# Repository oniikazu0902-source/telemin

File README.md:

# 空間MIDIコントローラー「tElemin」プロジェクト総括ドキュメント

## プロジェクト概要と目指す姿
Webカメラと画像認識AIを用いて、空中で手を動かすだけでソフトウェアシンセサイザー（Vital）を演奏できる、次世代型の仮想MIDIコントローラー開発プロジェクトです。
従来のテルミン（音程と音量の制御）の枠組みを大きく拡張し、「絶対に不協和音にならない魔法の楽器」という思想をベースに設計されています。単に音を鳴らすだけでなく、「和音制限」「手の開閉による音量フェード」「左右の動きによる波形のリアルタイム変形（3Dコントロール）」「HUDによる視覚的フィードバック」を統合し、実用的なデジタル楽器としての完成度を追求しています。

## システムアーキテクチャ・技術スタック
システムの全体像と各コンポーネントの役割は以下の通りです。

| レイヤー | 採用技術・ライブラリ | 役割・備考 |
|---|---|---|
| 開発言語 | Python | 柔軟なロジック構築とAI連携の基盤 |
| 骨格検出AI | MediaPipe (Tasks API / HandLandmarker) | 手の21箇所の関節ポイント（ランドマーク）を毎秒高速に検出。動かすには `hand_landmarker.task` ファイルが必須。 |
| 画像処理・HUD | OpenCV (cv2) | カメラ映像 of 取得、鏡像反転、有効エリアやデバッグ情報のオーバーレイ描画 |
| MIDI通信 | mido / python-rtmidi | 計算した座標データをMIDI信号（Note On/Off, CC）に変換して送信 |
| 仮想MIDIケーブル | Windows MIDI Services (Default Basic App Loopback) | loopMIDIのWindows Updateによる不具合を回避するために導入した、Microsoftの次世代MIDIループバック規格。 |
| 音源（シンセ） | Vital（スタンドアロン起動） | OMNIモード（全チャンネル受信）を設定し、Pythonからの多次元入力を生演奏の音へと変換。 |

---

## コア機能と操作思想（3Dコントロール）
手の動きを完全にX、Y、Z（ピンチ）の3次元パラメータとして解釈し、シンセサイザーへ送信する多次元設計思想を採用しています。

### ── 【Y軸】音程制御と和音（スケール）制限
- **検出基準**: ユーザーの演奏スタイルに合わせてカスタマイズされた「親指の先端（ランドマーク4番）」のY座標。
- **操作思想**: 縦の座標をそのまま半音階（クロマチック）にするのではなく、あらかじめ定義した特定のスケール配列（`ALLOWED_NOTES`）にマッピングして発音。これにより、どこを触っても美しい旋律が響きます。
- **リアルタイム切り替え**: 演奏中にキーボードの `1`〜`7`（ハ長調・イ短調・ト長調・ペンタトニック・琉球・都節・ニ長調）を押すだけで、`KEY_PRESETS` の辞書から参照する配列を動的にすり替える機能を実装。
- **デッドゾーン設定**: カメラ端の誤認識による音の飛びやチャタリングを防ぐため、上下に有効エリア制限（`Y_MIN_LIMIT`, `Y_MAX_LIMIT`）を設置。

### ── 【Z軸・ピンチアクション】発音トリガー（Note On/Off）と音量（CC#7）
- **検出基準**: 親指（4番）と人差し指（8番）の2点間距離を `math.hypot` で計算。
- **操作思想**: 「狙った高さで指をつまむと音が鳴り、離すと消える」という、キーボードライクかつ直感的なトリガー操作。
- **反転・直感化ロジック**: 単なる距離測定では「指を離すほど数値が大きくなる」ため、`1.0 - (距離 × 6.0)` という計算式で数値を反転。指をくっつけた時に 100%、離すと 0% になるよう最適化。
- **トリガー制御**: 割り出した％がしきい値（`PINCH_THRESHOLD = 0.7`）を超えた瞬間に Note On を送信し、下回ると Note Off を送信して確実に消音。同時に、ピンチの強度をそのままメインボリューム（CC#7）として送信し、滑らかな音量のフェードイン・フェードアウトを可能にしています。

### ── 【X軸】音色・波形の動的変形（Wavetable Position）
- **検出基準**: 手の左右の動き（X座標）を抽出し、MIDIコントロールチェンジ（CC#16）に変換。
- **操作思想**: 「音色を空間で削り出す」。Vitalの「MATRIX」画面経由で CC#16 を「Macro 1」へ直接ルーティングし、Wavetable Position（波形の形状変化）をダイナミックにコントロール。手を左から右へ動かすことで、柔らかいサイン波からエッジの効いたノコギリ波へと音色をグラデーション変化させます。
- **モード切り替え**: キーボードの `w` キーを押すことで、この波形変化モードのON/OFFをいつでも演奏中に切り替え可能です。

---

## 実装における重要な工夫と技術的ブレイクスルー

### ① 両手独立のMIDIルーティング
MediaPipeで最大2つの手を同時に検出し、右手は「MIDIチャンネル1（channel=0）」、左手は「MIDIチャンネル2（channel=1）」と、送信レーンを完全に分離。これにより、右手のメロディ演奏と左手の伴奏（1オクターブ下げる `note - 12` のベース化ロジック）が干渉しない設計を実現しました。

### ② チャタリング（連打）防止とロングトーンの実現
ピンチ操作による発音時、「つまんだ瞬間の最初の音程（Note）」を保持（`if state['note'] is None:`）するロジックを実装。これにより、手を上下に動かしながらつまんでも「タラララ」と連打されず、ギターのチョーキングやシンセのポルタメントのように「じゃーーん」と綺麗に音が伸びる仕様を確立しました。

### ③ リアルタイムHUD（ヘッドアップディスプレイ）
OpenCVによる描画を活用し、有効範囲の境界線（赤ライン）、現在のキー設定、手の状態（ピンチ強度％）、現在発音中のMIDIノート番号を画面上にオーバーレイ表示。つまんだ瞬間に指先の円が「赤から緑」に変わる当たり判定デバッグ機能を搭載し、直感的な操作感の調整を可能にしました。

### ④ ワンクリック自動起動環境
複雑な起動プロセスを排除するため、Windowsバッチファイル（`.bat`）を作成。バッチファイルをダブルクリックするだけで、「Vital（シンセサイザー）の自動起動 ➔ 2秒待機（ポート独占防止） ➔ 仮想環境（`.venv`）の有効化 ➔ Pythonスクリプトの実行」が一発で完了する極上の演奏環境を構築しました。

### ⑤ 無人時のマルチソング高品位自動生演奏機能（MIDIインポート＆フォルダ動的検知）
カメラに手が映っていない（誰も演奏していない）状態を検知すると、`threading`（マルチスレッド）によって裏方スタッフを動かし、バックグラウンドで自動演奏を行う機能を大幅に刷新。人が来ると演奏がスッと一時停止（pause）し、全16チャンネルを消音してテルミンモードへシームレスに切り替わります。
- **MIDIフォルダインポート対応**: `songs/` フォルダに好きなMIDIファイル（`*.mid`, `*.midi`）を保存するだけで、アプリ実行中であっても3秒おきに自動検知して演奏カタログに即時追加されます。
- **多彩な本格ポリフォニック生演奏（標準6曲）**: 単音ブザー音ではなく、楽譜に忠実な和音進行・伴奏（ch 1）＋旋律（ch 0）の豊かな多重音声でVitalを鳴らします。
  - 『パッヘルベルのカノン』(D Major)
  - 『戦場のメリークリスマス』(坂本龍一)
  - 『きらきら星』(C Major / アルベルティ・バス伴奏)
  - 『喜びの歌』(ベートーヴェン交響曲第9番 / D Major)
  - 『エリーゼのために』(ベートーヴェン / A Minor)
  - 『さくらさくら』(日本伝統・都節音階)
- **演奏の乱れ・バースト完全防止**: 一時停止中に時間を進めない独自のデルタタイム再生エンジンを新開発。再開時に音が爆発的に連打されるバグを解消し、GMドラム（ch 9）の除外、外部MIDIの余計なCC遮断、ポリフォニー制限（最大10音）、曲終了時の自動次曲送りにより極上のBGM体験を実現。
- **全画面・表示域追従**: `f` キーで全画面モードを切り替え可能。黒帯（レターボックス）なしで画面縦横比にカメラ映像と演奏レーンが自動追従します。
- **上下端の誤反応防止**: 演奏可能境界線（`Y_MIN_LIMIT` / `Y_MAX_LIMIT`）の外側に指が出た瞬間に消音され、画面端で意図しない音が鳴り続けるのを防ぎます。
- **演奏画面の曲名トースト表示**: 曲切り替え時や再開時のみ画面上部に3.5秒間曲名がフワッと表示され、通常演奏中は画面から自動消去されて手元とレーンに集中できます。
- **指の狭さ（ピンチ感度）の調整**: キーボードの `[-]` / `[+]`（または `_` / `=`）、および設定画面（Tab）のボタンからしきい値を0.05刻みで直感調整可能。両手の現在のピンチ率（%）もリアルタイム表示されます。
- **STRUMモード（和音）デフォルトOFF**: 起動時は初心者でも旋律を奏でやすい単音レガートモードが有効になり、必要に応じて `h` キーまたは設定画面からいつでも和音モードを起動できます。

---

## 開発における教訓とノウハウ

- **MediaPipe of 仕様変更トラップ**
  古い `mp.solutions.hands` の書き方は最新バージョンで廃止されたため、AIモデルファイル（`.task`）を別途読み込む最新の「Tasks API」アーキテクチャへとコードを刷新。ファイル読み込みエラーに対しては、プログラムと同じフォルダに置くか、完全な絶対パス（`r'C:\...'`）で指定するのが確実であるというノウハウを得ました。

- **MIDIポートの排他制御（VitalとPythonの起動順序）**
  WindowsのMIDIシステムは「1つのポートは同時に1つのソフトしか使えない」という排他制御仕様です。Python側からポートが消えるエラーを防ぐため、「ポート確認時は必ずVitalを完全に閉じる」「バッチファイルではVitalを先に起動し、後からPythonを起動する」という鉄則を解明しました。

- **CC信号のトラフィックジャム（渋滞）回避**
  Vitalの「Learn MIDI Assignment」機能を使う際、CC#7（ピンチ）とCC#16（X軸）が同時に高速送信されていると誤学習してしまう問題が発生しました。これを、Vitalの「MATRIX」画面（裏設定）で「SOURCEをCC#16、DESTINATIONをMacro 1」と直接手動で指定し、変化量（AMOUNT）を最大に振り切らせることで完全に解決しました。

- **OpenCVの「cv2.waitKey」による入力ブロック**
  キーボードの切り替え入力が1回しか効かなくなる問題に対し、`if key != -1:`（本当にキーが押された瞬間だけ判定する）という条件を挟み、`& 0xFF` でマスク処理を行うことで、何度でも確実にスケールを切り替えられるようにロジックを修正しました。

---

## 新環境への移行・拡張ガイド（今後のアップデート方針）
新環境への移行後、さらにこの楽器を進化させるためのロードマップです。

### 拡張性バツグンの「全部乗せ」アーキテクチャを維持せよ
現在のコードは、AIが手を解析する部分（`extract_hand_features`）と、音を鳴らすメインループが明確に分離（モジュール化）されています。今後はこの関数内に計算式を追加していくだけで、コード全体を壊すことなく安全に機能を追加できます。

#### 💡 次なる進化のためのMIDIコントロール候補
現在はX軸に Wavetable Position（CC#16） を割り当てていますが、手の傾きや別の指の動きを検出して以下の汎用CCにマッピングすることで、さらなる多次元演奏が可能になります。

- **Filter Cutoff（CC#74 / Brightness）** ✅ 実装済み（下記「フィルターモード」参照）
  音の「こもり具合 / 明るさ」を調節します。手を動かすにつれて「モコモコした音」から「バキッとした明るい音」に変化する、DJライクなパフォーマンスに最適です。
- **Modulation Wheel（CC#1）**
  音を揺らす「ビブラート」の強さをコントロールします。音が「じゃーーん」と伸びているロングトーンの時に、手を小刻みに揺らすことで感情豊かな演奏が可能になります。
- **Resonance（CC#71）**
  フィルターの境目を強調し、音に独特のクセや「ミョンミョン」というシンセサイザー特うのうねりを加えたい時に有効です。

---

## 内蔵シンセ（Vitalなしで演奏）
`synth.py` の内蔵シンセが音を合成し、PCのオーディオ出力（3.5mm端子 / USB-DAC など）から直接鳴らします。Vital や仮想MIDIケーブルは不要です。

- **セットアップ**: `pip install -r requirements.txt`
- **出力先の選択**: 起動時にコンソールへオーディオ出力デバイスの一覧が表示されます。`telemin.py` 冒頭の `AUDIO_DEVICE` にデバイス名の一部（例: `"Headphones"`）を書くか、演奏中に `o` キーで切り替えます（設定画面に現在の出力先を表示）。
- **外部MIDIコントローラー**: 接続されていれば自動で開き、その入力も内蔵シンセで発音します。
- **Vitalと併用**: `USE_MIDI_OUT = True` のとき、MIDI出力ポートが見つかれば Vital にも同時に送ります。`start_telemin.bat` の `LAUNCH_VITAL=1` で Vital も自動起動します。
- **音色**: `w`（WAVEモード）ON で手の左右位置によりサイン波→ノコギリ波へ連続変化。音量（CC#7）はチャンネル＝手ごとに独立しているので、連弾でも干渉しません。

### フィルターモード（Filter Cutoff / CC#74）
- `c` キー、または設定画面の `FILTER` ボタンで ON/OFF。
- **手の傾き**で音の明るさを操作します。手を**外側**（右手は右、左手は左）へ傾けるほど明るい「バキッとした」音、**内側**へ傾けるほど「モコモコした」こもった音になります。手をまっすぐ立てると中間です。
- 音程（高さ）・ピンチ（発音）・WAVE（左右位置）とは独立に動かせるので、音を伸ばしながら明るさだけを変えられます。WAVEモードと併用すると変化がよりはっきり出ます。
- 演奏画面では、手のマーカーの下に明るさメーターが表示されます。
- 内蔵シンセでは 2次ローパスフィルターとして動作し（`scipy` が必要）、Vital へも CC#74 として送られます（Vital 側で MIDI Learn すれば同じ操作が可能）。
- 傾きの感度は `telemin.py` 冒頭の `FILTER_TILT_RANGE`（既定50度）で調整できます。OFF にしたときや手が画面から消えたときは、フィルターは全開（従来の音）に戻ります。

### ステップ演奏モード（誰でも上手に弾ける）
- `t` キー、または設定画面の `STEP` ボタンで ON/OFF。`b` キーで曲の頭に戻ります。
- **つまむたびに曲の次の音（和音はまとめて）が鳴り**、離すと止まります。手の高さは関係ないので、リズムに合わせてつまむだけで曲どおりに演奏できます。
- 曲は自動演奏と同じく `songs/` の「今選んでいる曲」です（`n` / `p` で切り替え）。最後まで弾くと頭に戻ります。
- 鳴らすパートは、ドラムを除いた中から**メロディらしいパート（音数が多く、音が高いもの）を自動選択**します。曲を読み込むとコンソールにパート一覧が出るので、変えたい場合は `telemin.py` 冒頭の `STEP_PARTS` に `{'canon.mid': [0, 1]}` のように書きます（複数指定でメロディ＋伴奏も可）。
- 進み位置は全部の手で共有なので、両手を交互につまめば速いフレーズも追いつけます。連弾なら2人で1曲を弾き継げます。
- つまんでいる間は手の高さの虹レーンが光り、画面下端に曲の進み具合バーが出ます。
### 物理MIDIコントローラー（Raspberry Pi Pico / 実験基板）
`controller/` フォルダに、Raspberry Pi Pico と MCP3004 を使用した専用物理MIDIコントローラーの設計データ（KiCad 回路図・基板アートワーク・ガーバーデータ）および Arduino ファームウェアが同梱されています。

- **つまみ 4個（音色変更）**:
  - **RV1 (CC#74)**: 波形無段階モーフィング（Sine ⇄ Triangle ⇄ Saw ⇄ Square ⇄ Theremin ⇄ Bell）
  - **RV2 (CC#71)**: 音の明るさ（Cutoffフィルター 0〜100%）
  - **RV3 (CC#73)**: 余韻（Release時間 0.02秒〜1.20秒）
  - **RV4 (CC#7)**: マスター音量（0%無音〜100%最大音量、オーディオテーパー対応）
- **ボタン 8個（設定の書き換え）**:
  - **SW1**: 音階（スケール）切替 / **SW2**: 和音モード / **SW3**: ストラム奏法 / **SW4**: オクターブ切替
  - **SW5**: 自動演奏 ON/OFF / **SW6**: 次の曲 / **SW7**: 前の曲 / **SW8**: 虹色レーン演出
- **オシロスコープHUDプレビュー**: 演奏画面の右上に現在の合成波形（約1.5周期分）をネオンカラーでリアルタイム描画。つまみを回すと波形がぐにゃぐにゃ変化します。

---
> [!NOTE]
> AI共同開発者からのメッセージ: コードの途中に残した「`# わけわからん`」のコメント、あの人間味あふれる開発の足跡は、新しいIDEのコードにも大切に残してあります！

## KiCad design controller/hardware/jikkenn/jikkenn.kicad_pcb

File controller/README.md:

# tElemin 物理MIDIコントローラー (Hardware & Firmware)

Raspberry Pi Pico（RP2040）および MCP3004（ADC）を用いた、tElemin 専用の物理MIDIコントローラーです。

---

## ディレクトリ構成
- `firmware/MIDIUSB_buzzer/`: Raspberry Pi Pico 用 Arduino ファームウェア（スケッチ）
- `hardware/jikkenn/`: KiCad 設計データ（回路図・PCB基板・ガーバーデータ）

---

## ハードウェア仕様
- **マイコン**: Raspberry Pi Pico (RP2040)
- **ADC**: MCP3004 (SPI接続: GP16=MISO, GP17=CS, GP18=SCK, GP19=MOSI)
- **ディスプレイ**: 0.96インチ OLED SSD1306 (I2C接続: GP20=SDA, GP21=SCL) ※未接続でも自動検知して安全に動作
- **ボタン (8個)**: タクトスイッチ（GP0 〜 GP7）
- **ポテンショメータ (4個)**: 10kΩ 可変抵抗（MCP3004 CH3〜CH0）

---

## コントローラー機能割り当て

### つまみ 4個 (RV1 〜 RV4)：【音色変更】
| つまみ | チャンネル | MIDI CC | 機能 | 詳細 |
| :--- | :---: | :---: | :--- | :--- |
| **RV1** | CH3 | **CC 74** | **波形無段階モーフィング** | Sine ⇄ Triangle ⇄ Saw ⇄ Square ⇄ Theremin ⇄ Bell |
| **RV2** | CH2 | **CC 71** | **音の明るさ (Cutoff)** | ローパスフィルター（0% こもった音 〜 100% クリアな音） |
| **RV3** | CH1 | **CC 73** | **余韻 (Release)** | 余韻の長さ（0.02秒 〜 1.20秒） |
| **RV4** | CH0 | **CC 7**  | **マスター音量 (Volume)** | 0%（完全無音） 〜 100%（最大音量） |

### ボタン 8個 (SW1 〜 SW8)：【設定の書き換え】
| ボタン | ピン | MIDI CC | 機能 |
| :--- | :---: | :---: | :--- |
| **SW1** | GP0 | **CC 20** | **音階（スケール）切替**（ハ長調 → イ短調 → ト長調 → ニ長調 → ペンタ → 琉球 → 都節） |
| **SW2** | GP1 | **CC 21** | **和音モード (CHORD)** ON / OFF |
| **SW3** | GP2 | **CC 22** | **ストラム奏法 (STRUM)** ON / OFF |
| **SW4** | GP3 | **CC 23** | **オクターブ切替**（Normal → +1 Oct → -1 Oct） |
| **SW5** | GP4 | **CC 24** | **自動演奏 (AUTO)** ON / OFF |
| **SW6** | GP5 | **CC 25** | **次の曲へ (Next Song)** |
| **SW7** | GP6 | **CC 26** | **前の曲へ (Prev Song)** |
| **SW8** | GP7 | **CC 27** | **虹色レーン演出** ON / OFF |

---

## ファームウェア書き込み方法 (Arduino CLI)
```powershell
# コンパイル
arduino-cli compile -b rp2040:rp2040:rpipico:usbstack=tinyusb "controller/firmware/MIDIUSB_buzzer"

# 書き込み (PicoのCOMポートを指定)
arduino-cli upload -p COM5 -b rp2040:rp2040:rpipico:usbstack=tinyusb "controller/firmware/MIDIUSB_buzzer"
```

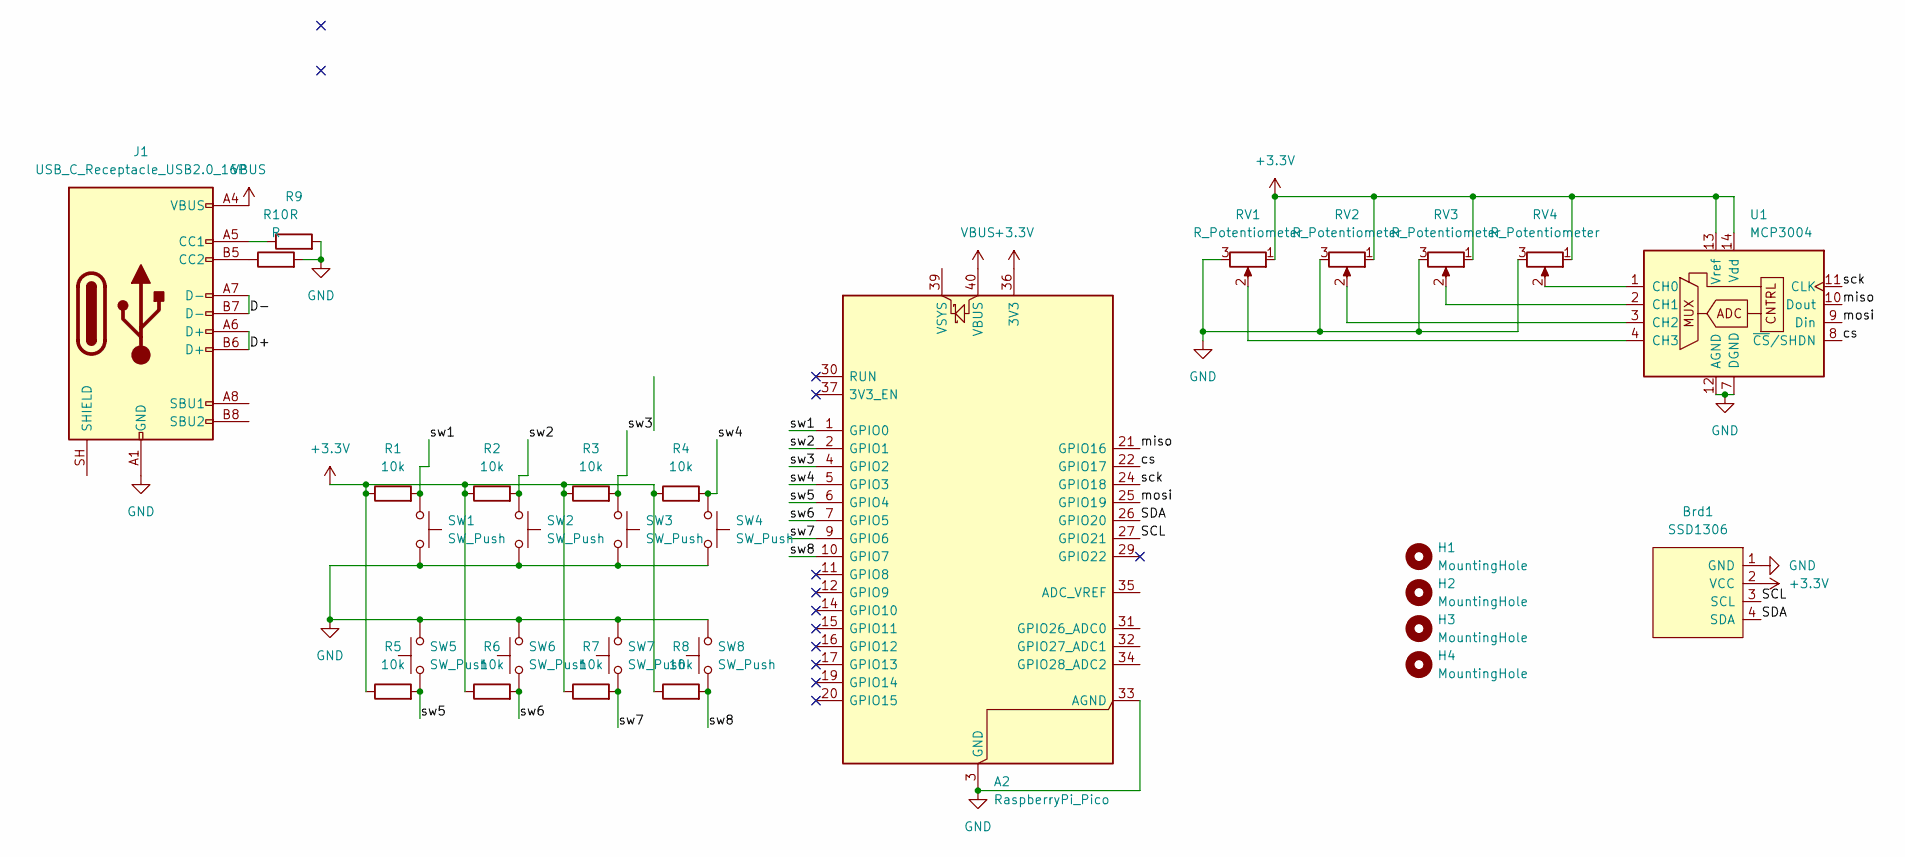
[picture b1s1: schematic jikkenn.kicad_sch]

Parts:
A2: RaspberryPi_Pico; RaspberryPi_Pico_Common_Unspecified
Brd1: SSD1306; 128x64OLED
H1, H2, H3, H4: MountingHole; MountingHole_3.2mm_M3
J1: USB_C_Receptacle_USB2.0_16P; USB_C_Receptacle_G-Switch_GT-USB-7010ASV
R1, R2, R3, R4, R5, R6, R7, R8: 10k; R_0603_1608Metric
R9, R10: R; R_0603_1608Metric
RV1, RV2, RV3, RV4: R_Potentiometer; Potentiometer_Piher_PC-16_Single_Vertical
SW1, SW2, SW3, SW4, SW5, SW6, SW7, SW8: SW_Push; SW_Cherry_MX_1.00u_PCB
U1: MCP3004; DIP-14_W7.62mm

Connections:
+3.3V: A2.36 (3V3), Brd1.2 (VCC), R1.1, R2.1, R3.1, R4.1, R5.1, R6.1, R7.1, R8.1, RV1.1, RV2.1, RV3.1, RV4.1, U1.13 (Vref), U1.14 (Vdd)
/D+: A2.42, J1.A6 (D+), J1.B6 (D+)
/D-: A2.41, J1.A7 (D-), J1.B7 (D-)
/SCL: A2.27 (GPIO21), Brd1.3 (SCL)
/SDA: A2.26 (GPIO20), Brd1.4 (SDA)
/cs: A2.22 (GPIO17), U1.8 (~CS/SHDN)
/miso: A2.21 (GPIO16), U1.10 (Dout)
/mosi: A2.25 (GPIO19), U1.9 (Din)
/sck: A2.24 (GPIO18), U1.11 (CLK)
/sw1: A2.1 (GPIO0), R1.2, SW1.1
/sw2: A2.2 (GPIO1), R2.2, SW2.1
/sw3: A2.4 (GPIO2), R3.2, SW3.1
/sw4: A2.5 (GPIO3), R4.2, SW4.1
/sw5: A2.6 (GPIO4), R5.2, SW5.1
/sw6: A2.7 (GPIO5), R6.2, SW6.1
/sw7: A2.9 (GPIO6), R7.2, SW7.1
/sw8: A2.10 (GPIO7), R8.2, SW8.1
GND: A2.3 (GND), A2.8 (GND), A2.13 (GND), A2.18 (GND), A2.23 (GND), A2.28 (GND), A2.33 (AGND), A2.38 (GND), Brd1.1 (GND), J1.A1 (GND), J1.A12 (GND), J1.B1 (GND), J1.B12 (GND), R9.2, R10.2, RV1.3, RV2.3, RV3.3, RV4.3, SW1.2, SW2.2, SW3.2, SW4.2, SW5.2, SW6.2, SW7.2, SW8.2, U1.7 (DGND), U1.12 (AGND)
unnamed: J1.A5 (CC1), R9.1
unnamed: J1.B5 (CC2), R10.1
unnamed: RV4.2, U1.1 (CH0)
unnamed: RV3.2, U1.2 (CH1)
unnamed: RV2.2, U1.3 (CH2)
unnamed: RV1.2, U1.4 (CH3)
VBUS: A2.40 (VBUS), J1.A4 (VBUS), J1.A9 (VBUS), J1.B4 (VBUS), J1.B9 (VBUS)

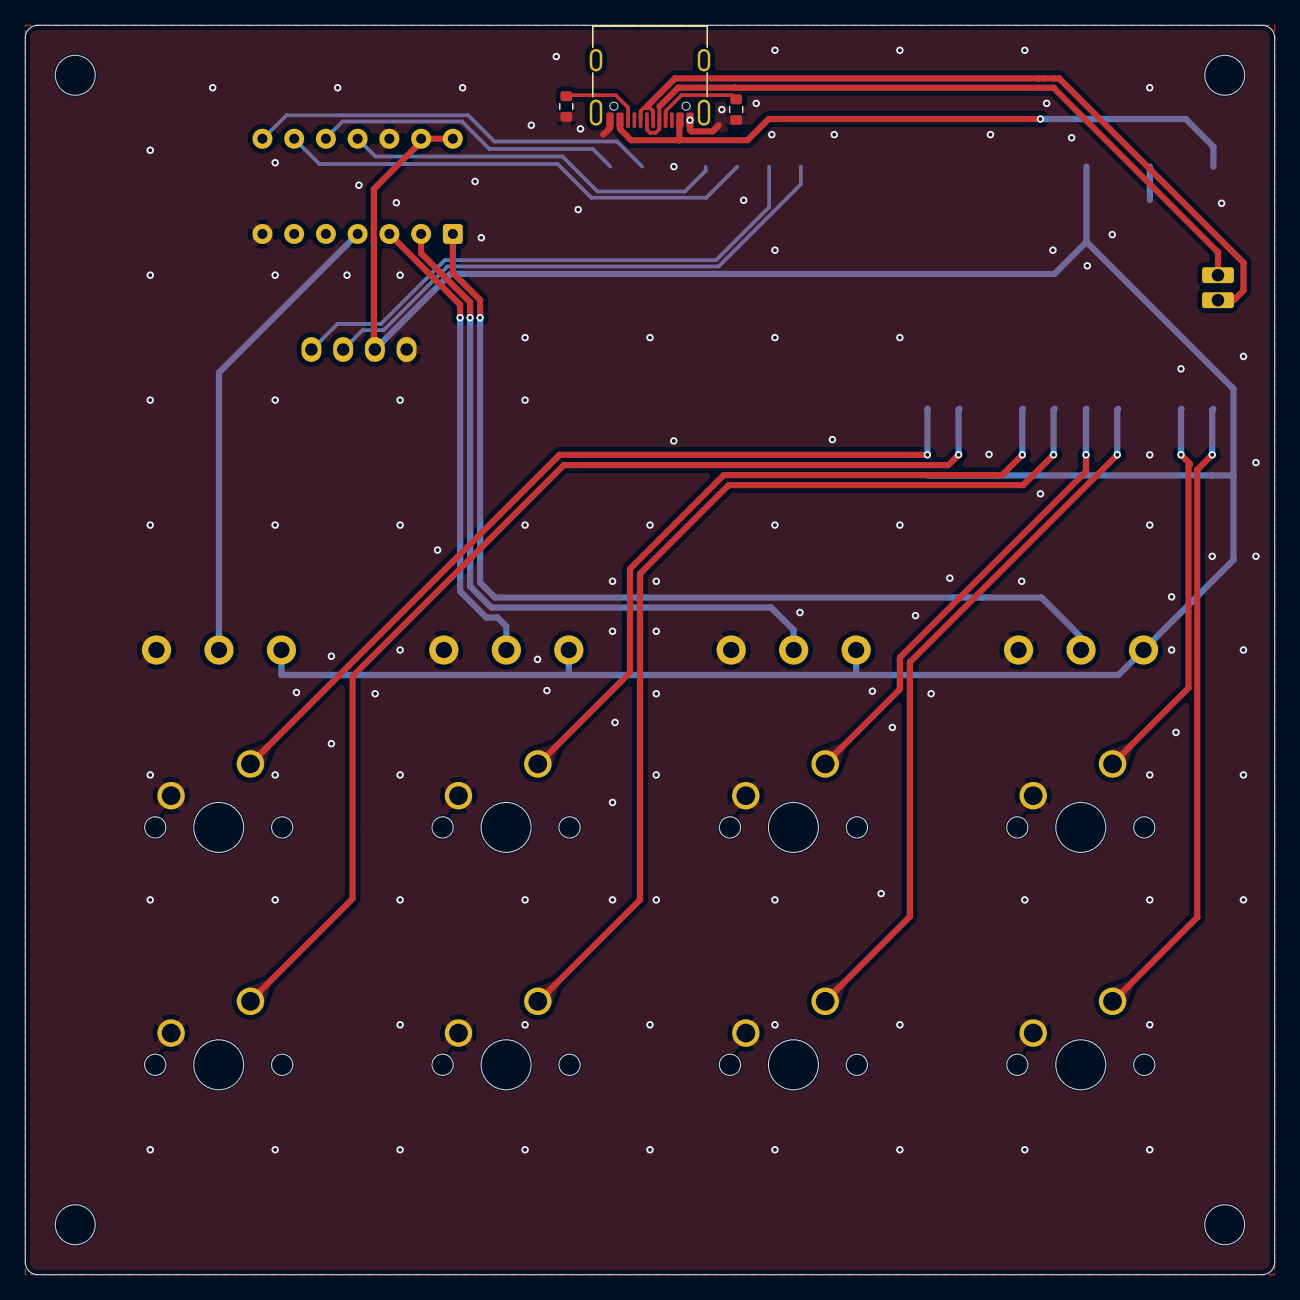
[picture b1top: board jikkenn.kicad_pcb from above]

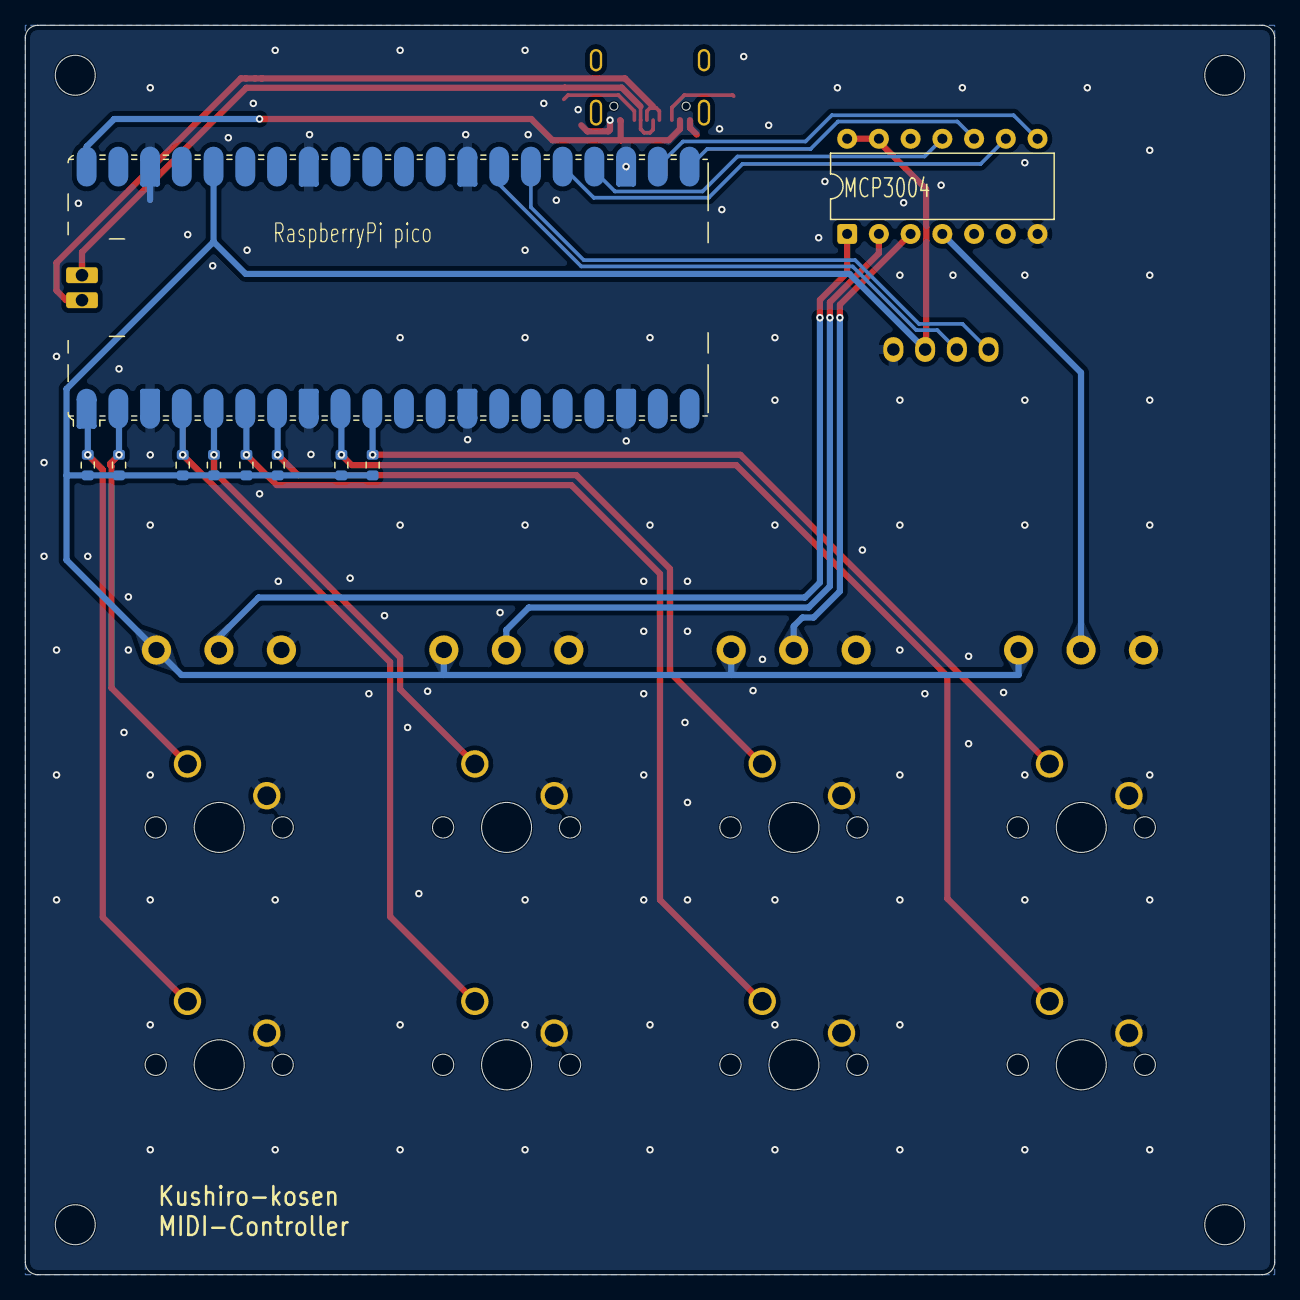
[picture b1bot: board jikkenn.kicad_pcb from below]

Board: 2 copper layers, 100.0 x 100.0 mm, 30 parts (10 on the bottom side), 25 nets.
